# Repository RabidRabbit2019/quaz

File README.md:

# quaz
ветка проекта для платы на основе STM32G431CBU6

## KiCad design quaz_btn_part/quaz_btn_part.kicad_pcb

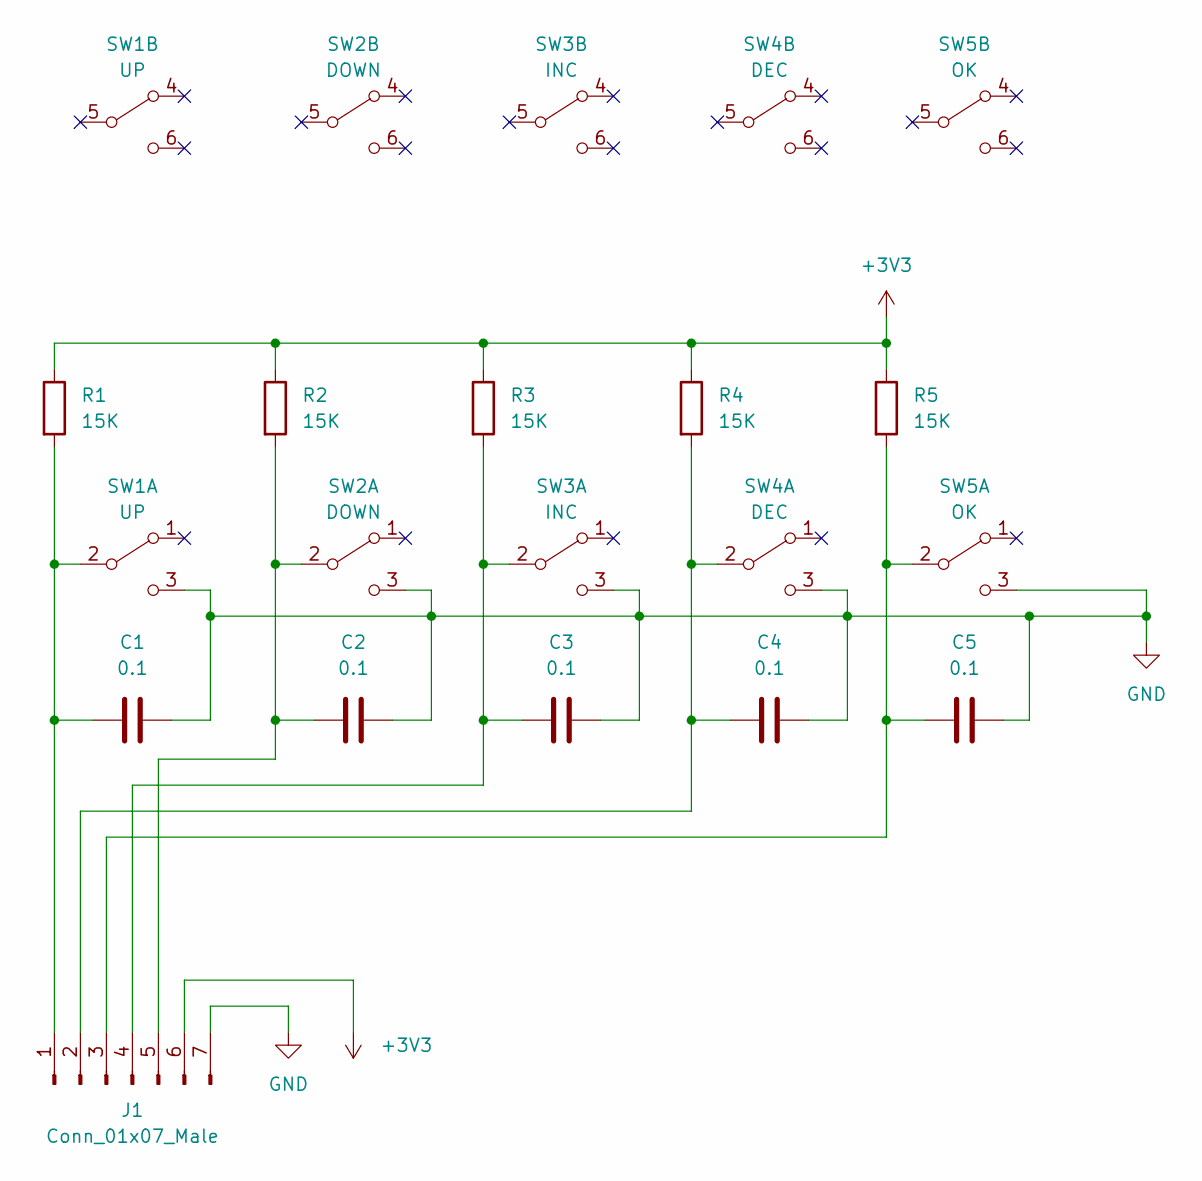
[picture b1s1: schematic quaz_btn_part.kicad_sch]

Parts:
C1, C2, C3, C4, C5: 0.1; C_1206_3216Metric_Pad1.33x1.80mm_HandSolder
J1: Conn_01x07_Male; PinHeader_1x07_P2.54mm_Vertical
R1, R2, R3, R4, R5: 15K; R_1206_3216Metric_Pad1.30x1.75mm_HandSolder
SW1: UP; BTN13
SW2: DOWN; BTN13
SW3: INC; BTN13
SW4: DEC; BTN13
SW5: OK; BTN13

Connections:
+3V3: J1.6, R1.1, R2.1, R3.1, R4.1, R5.1
GND: C1.2, C2.2, C3.2, C4.2, C5.2, J1.7, SW1.3 (C), SW2.3 (C), SW3.3 (C), SW4.3 (C), SW5.3 (C)
unnamed: C2.1, J1.5, R2.2, SW2.2 (B)
unnamed: C3.1, J1.4, R3.2, SW3.2 (B)
unnamed: C4.1, J1.2, R4.2, SW4.2 (B)
unnamed: C5.1, J1.3, R5.2, SW5.2 (B)
unnamed: C1.1, J1.1, R1.2, SW1.2 (B)

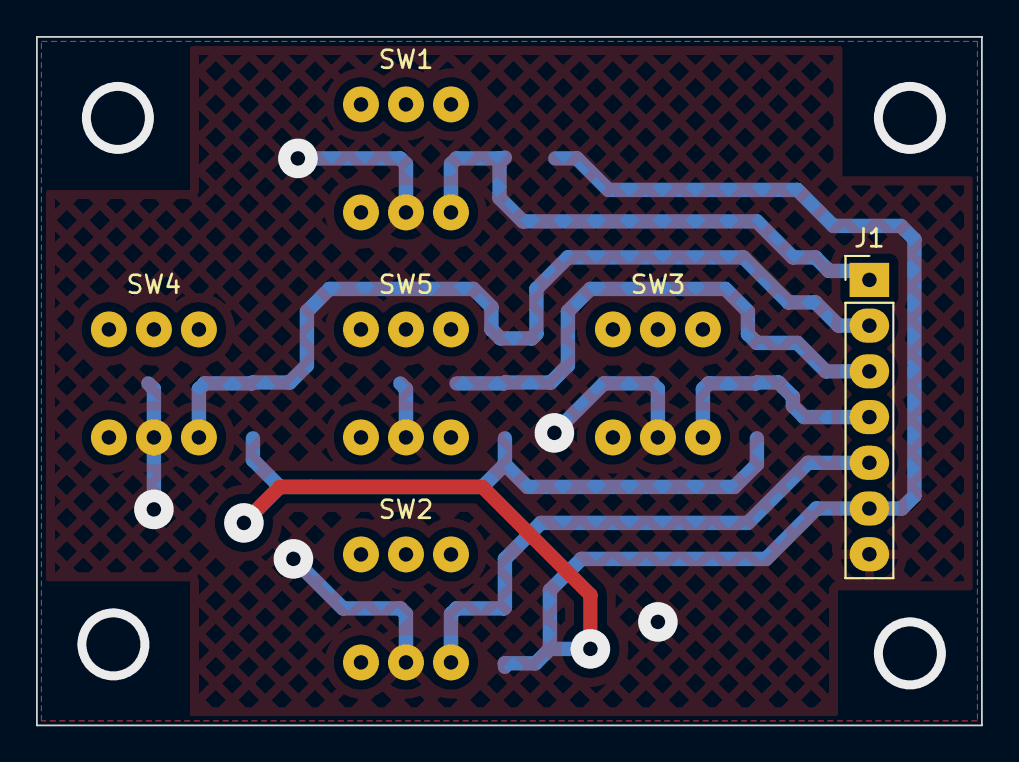
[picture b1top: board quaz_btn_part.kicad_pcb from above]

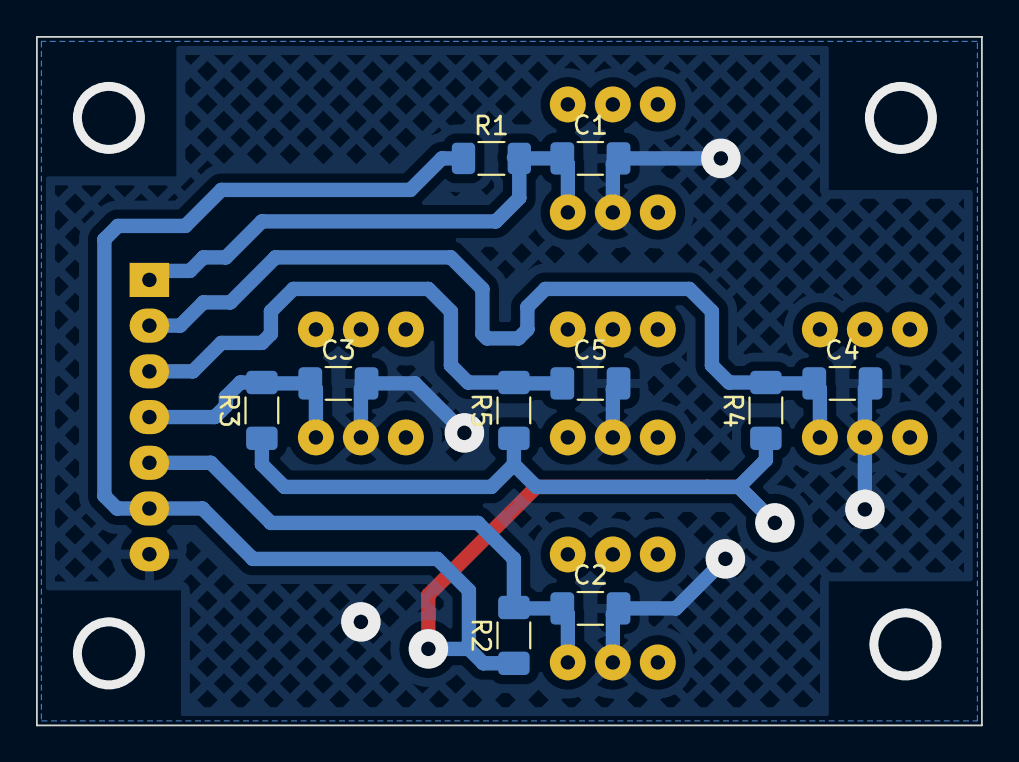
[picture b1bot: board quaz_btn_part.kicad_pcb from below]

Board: 2 copper layers, 52.5 x 38.2 mm, 16 parts (10 on the bottom side), 7 nets.

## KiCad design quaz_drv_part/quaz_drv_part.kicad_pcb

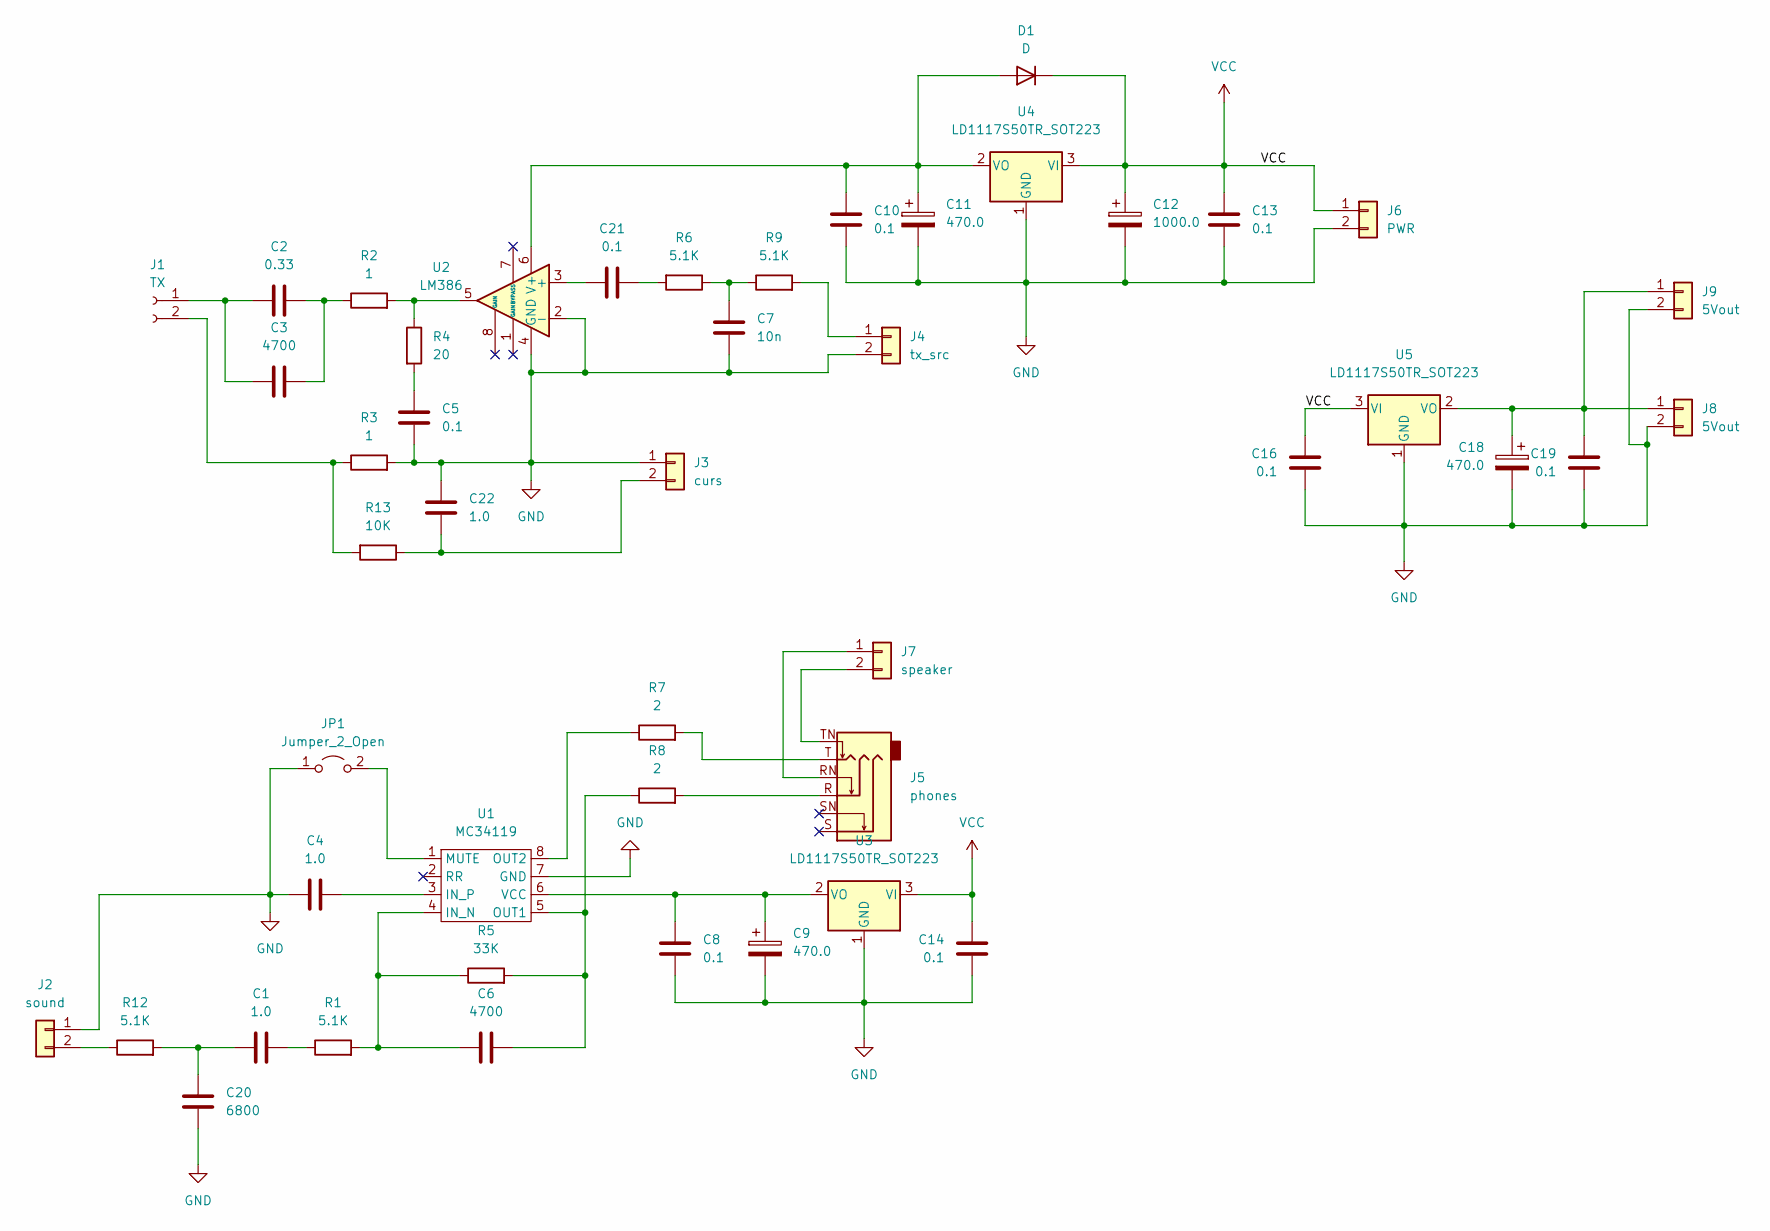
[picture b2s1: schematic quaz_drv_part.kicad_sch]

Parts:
C1, C4, C22: 1.0; C_1206_3216Metric_Pad1.33x1.80mm_HandSolder
C2: 0.33; C_Disc_D9.0mm_W5.0mm_P5.00mm
C3, C6: 4700; C_Disc_D9.0mm_W5.0mm_P5.00mm
C5, C8, C10, C13, C14, C16, C19, C21: 0.1; C_1206_3216Metric_Pad1.33x1.80mm_HandSolder
C7: 10n; C_Disc_D9.0mm_W5.0mm_P5.00mm
C9: 470.0; CP_Radial_D8.0mm_P5.00mm
C11, C18: 470.0; CP_Radial_D10.0mm_P5.00mm
C12: 1000.0; CP_Radial_D10.0mm_P5.00mm
C20: 6800; C_Disc_D9.0mm_W5.0mm_P5.00mm
D1: D; D_DO-41_SOD81_P5.08mm_Vertical_KathodeUp
J1: TX; PinHeader_1x02_P2.54mm_Vertical
J2: sound; PinHeader_1x02_P2.54mm_Vertical
J3: curs; PinHeader_1x02_P2.54mm_Vertical
J4: tx_src; PinHeader_1x02_P2.54mm_Vertical
J5: phones; Jack_6.35mm_Neutrik_NMJ6HCD3_Horizontal
J6: PWR; PinHeader_1x02_P2.54mm_Vertical
J7: speaker; PinHeader_1x02_P2.54mm_Vertical
J8, J9: 5Vout; PinHeader_1x02_P2.54mm_Vertical
JP1: Jumper_2_Open; PinHeader_1x02_P2.54mm_Vertical
R1, R6, R9, R12: 5.1K; R_1206_3216Metric_Pad1.30x1.75mm_HandSolder
R2, R3: 1; R_Axial_Power_L20.0mm_W6.4mm_P7.62mm_Vertical
R4: 20; R_Axial_DIN0207_L6.3mm_D2.5mm_P5.08mm_Vertical
R5: 33K; R_1206_3216Metric_Pad1.30x1.75mm_HandSolder
R7, R8: 2; R_1206_3216Metric_Pad1.30x1.75mm_HandSolder
R13: 10K; R_1206_3216Metric_Pad1.30x1.75mm_HandSolder
U1: MC34119; SOIC-8_3.9x4.9mm_P1.27mm
U2: LM386; DIP-8_W7.62mm
U3, U4, U5: LD1117S50TR_SOT223; SOT-223-3_TabPin2

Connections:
GND: C4.1, C5.2, C7.2, C8.2, C9.2, C10.2, C11.2, C12.2, C13.2, C14.2, C16.2, C18.2, C19.2, C20.2, C22.2, J2.1, J3.1, J4.2, J6.2, J8.2, J9.2, JP1.1 (A), R3.2, U1.7 (GND), U2.2 (-), U2.4 (GND), U3.1 (GND), U4.1 (GND), U5.1 (GND)
unnamed: C1.1, C20.1, R12.2
unnamed: C1.2, R1.1
unnamed: C2.1, C3.1, J1.1
unnamed: C2.2, C3.2, R2.1
unnamed: C4.2, U1.3 (IN_P)
unnamed: C5.1, R4.2
unnamed: C6.1, R5.2, R8.1, U1.5 (OUT1)
unnamed: C6.2, R1.2, R5.1, U1.4 (IN_N)
unnamed: C7.1, R6.1, R9.1
unnamed: C8.1, C9.1, U1.6 (VCC), U3.2 (VO)
unnamed: C10.1, C11.1, D1.2 (A), U2.6 (V+), U4.2 (VO)
unnamed: C18.1, C19.1, J8.1, J9.1, U5.2 (VO)
unnamed: C21.1, U2.3 (+)
unnamed: C21.2, R6.2
unnamed: C22.1, J3.2, R13.1
unnamed: J1.2, R3.1, R13.2
unnamed: J2.2, R12.1
unnamed: J4.1, R9.2
unnamed: J5.R, R8.2
unnamed: J5.RN, J7.1
unnamed: J5.T, R7.2
unnamed: J5.TN, J7.2
unnamed: JP1.2 (B), U1.1 (MUTE)
unnamed: R2.2, R4.1, U2.5
unnamed: R7.1, U1.8 (OUT2)
VCC: C12.1, C13.1, C14.1, C16.1, D1.1 (K), J6.1, U3.3 (VI), U4.3 (VI), U5.3 (VI)

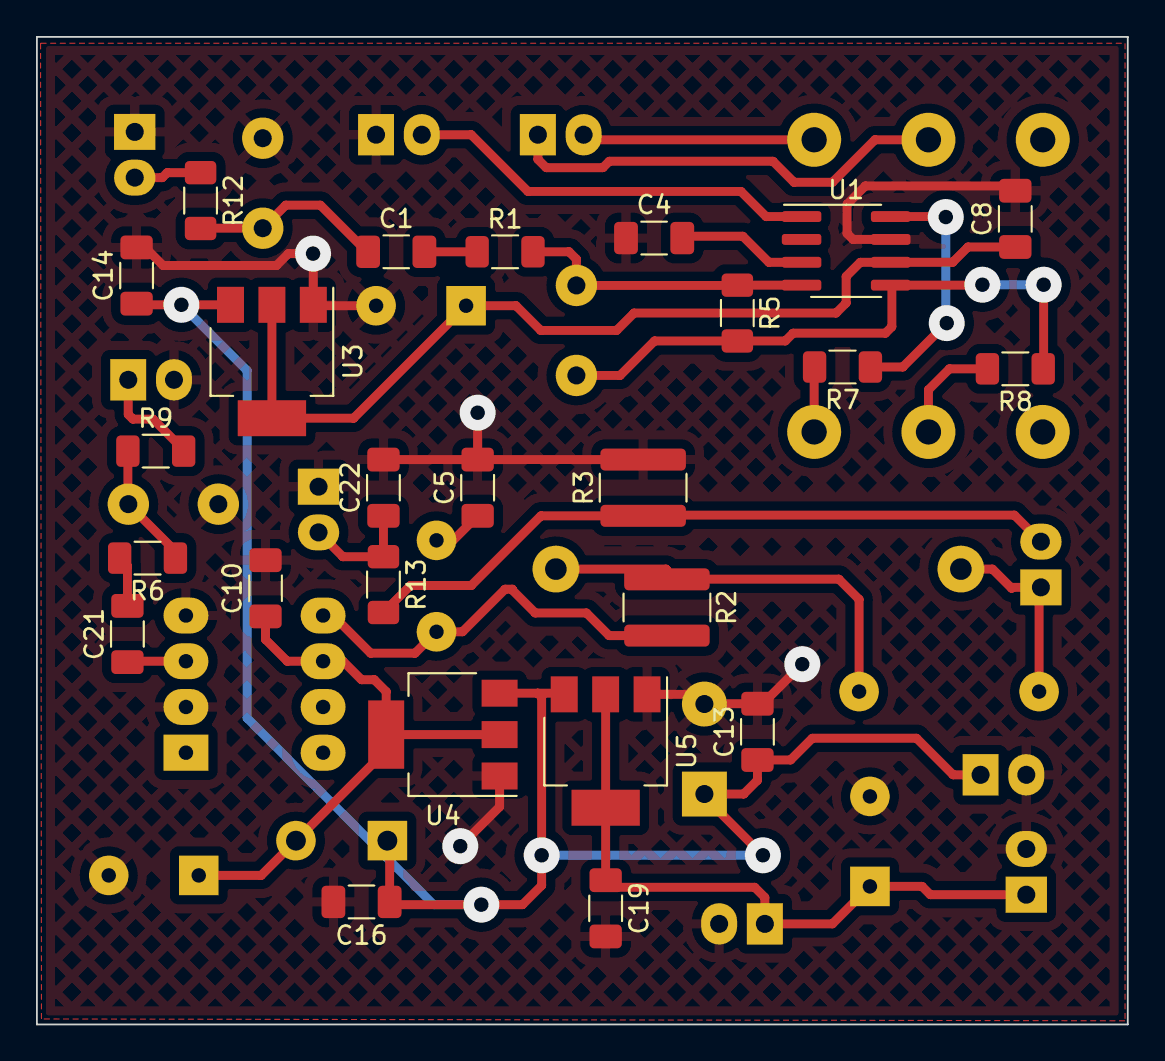
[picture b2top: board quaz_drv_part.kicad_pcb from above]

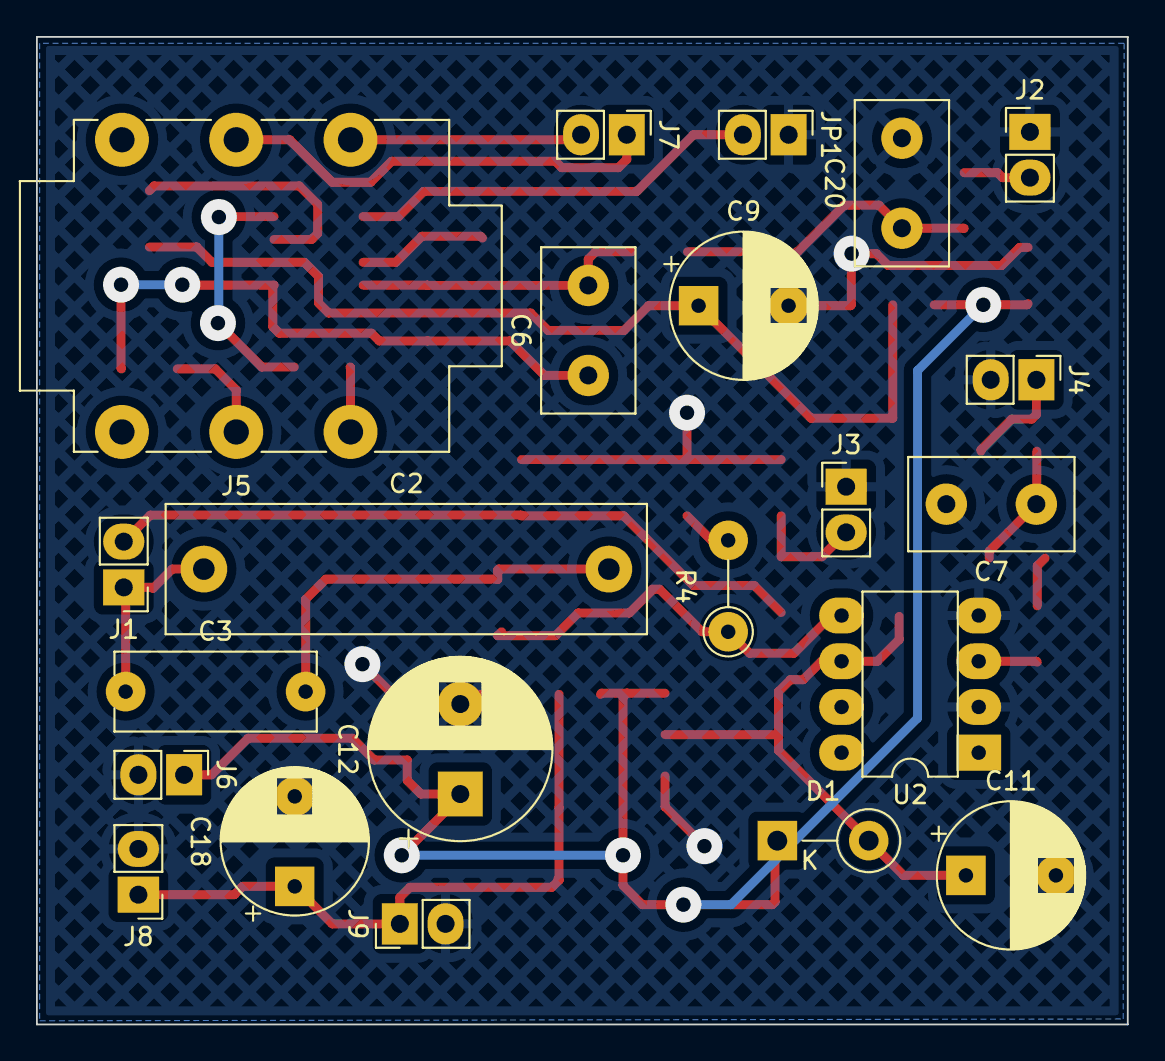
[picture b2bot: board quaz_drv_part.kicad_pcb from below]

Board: 2 copper layers, 60.6 x 54.9 mm, 47 parts (22 on the bottom side), 27 nets.

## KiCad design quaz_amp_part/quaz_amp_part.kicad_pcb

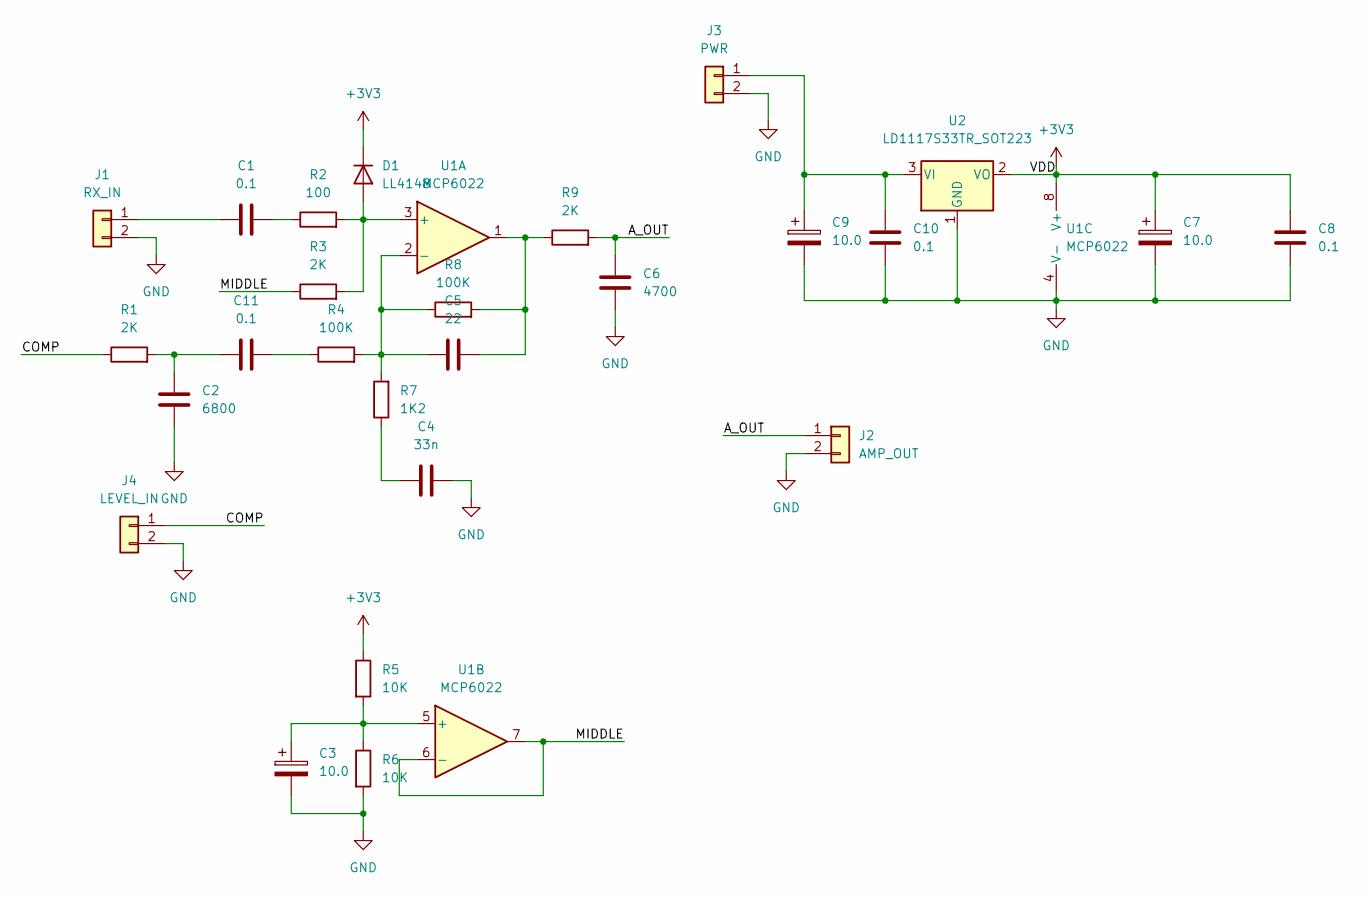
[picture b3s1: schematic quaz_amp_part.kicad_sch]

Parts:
C1, C8, C10, C11: 0.1; C_1206_3216Metric_Pad1.33x1.80mm_HandSolder
C2: 6800; C_Disc_D3.4mm_W2.1mm_P2.50mm
C3: 10.0; CP_EIA-7132-28_AVX-C_Pad2.72x3.50mm_HandSolder
C4: 33n; C_Disc_D8.0mm_W2.5mm_P5.00mm
C5: 22; C_Disc_D8.0mm_W2.5mm_P5.00mm
C6: 4700; C_Disc_D3.4mm_W2.1mm_P2.50mm
C7, C9: 10.0; CP_EIA-7132-20_AVX-U_Pad2.72x3.50mm_HandSolder
D1: LL4148; D_1206_3216Metric_Pad1.42x1.75mm_HandSolder
J1: RX_IN; PinHeader_1x02_P2.54mm_Vertical
J2: AMP_OUT; PinHeader_1x02_P2.54mm_Vertical
J3: PWR; PinHeader_1x02_P2.54mm_Vertical
J4: LEVEL_IN; PinHeader_1x02_P2.54mm_Vertical
R1, R3, R9: 2K; R_1206_3216Metric_Pad1.30x1.75mm_HandSolder
R2: 100; R_1206_3216Metric_Pad1.30x1.75mm_HandSolder
R4, R8: 100K; R_1206_3216Metric_Pad1.30x1.75mm_HandSolder
R5, R6: 10K; R_1206_3216Metric_Pad1.30x1.75mm_HandSolder
R7: 1K2; R_1206_3216Metric_Pad1.30x1.75mm_HandSolder
U1: MCP6022; SOIC-8_3.9x4.9mm_P1.27mm
U2: LD1117S33TR_SOT223; SOT-223-3_TabPin2

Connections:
+3V3: C7.1, C8.1, D1.1 (K), R5.1, U1.8 (V+), U2.2 (VO)
/A_OUT: C6.2, J2.1, R9.2
/COMP: J4.1, R1.1
/MIDDLE: R3.1, U1.6 (-), U1.7
GND: C2.2, C3.2, C4.2, C6.1, C7.2, C8.2, C9.2, C10.2, J1.2, J2.2, J3.2, J4.2, R6.2, U1.4 (V-), U2.1 (GND)
unnamed: C1.1, J1.1
unnamed: C1.2, R2.1
unnamed: C2.1, C11.1, R1.2
unnamed: C3.1, R5.2, R6.1, U1.5 (+)
unnamed: C4.1, R7.1
unnamed: C5.1, R4.2, R7.2, R8.1, U1.2 (-)
unnamed: C5.2, R8.2, R9.1, U1.1
unnamed: C9.1, C10.1, J3.1, U2.3 (VI)
unnamed: D1.2 (A), R2.2, R3.2, U1.3 (+)
unnamed: C11.2, R4.1

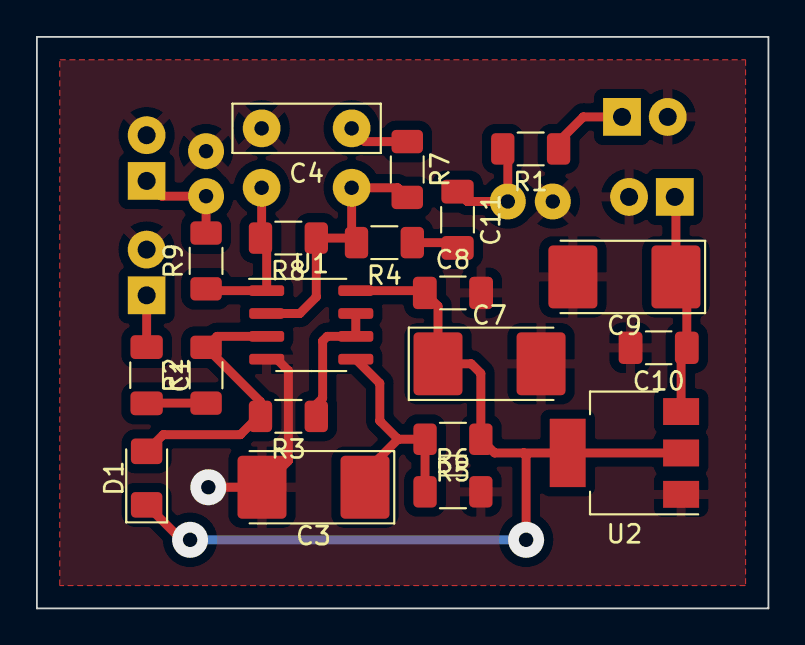
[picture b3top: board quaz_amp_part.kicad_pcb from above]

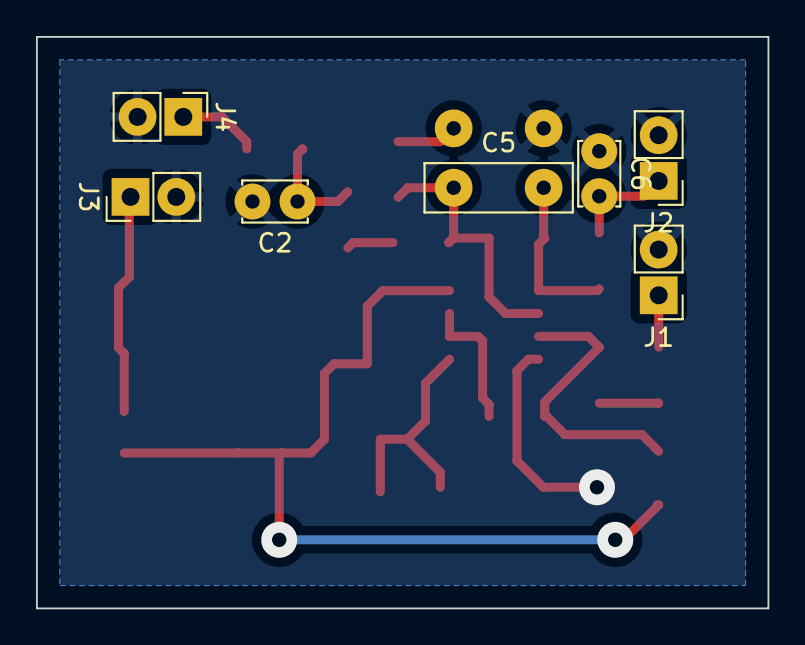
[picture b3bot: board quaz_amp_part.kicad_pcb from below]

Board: 2 copper layers, 40.6 x 31.8 mm, 27 parts (7 on the bottom side), 15 nets.

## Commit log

2024-03-18 initial, dds works
2024-03-19 adc double buffered
2024-03-20 next
2024-03-25 attach display test
2024-03-26 some minor changes
2024-03-27 change font
2024-03-29 add kicad sources
2024-03-29 more settings
2024-03-30 settings next
2024-04-01 buttons, gui
2024-04-13 use CORDIC arctan for vector length instead sqrt()
2024-04-15 drv layout change
2024-04-19 add btn_part
2024-04-25 add menu nav
2024-05-04 add current sens
2024-05-06 add rx settings
2024-05-06 fix buttons
2024-05-07 add buttons board
2024-05-15 add some settings
2024-05-16 remove some code
2024-06-14 pcb for buttons
2024-10-23 добавлены настройки вольтметра
2024-12-25 комментарии, новая версия файла stm32f103x6.h
2024-12-25 remove extra
2024-12-25 ветка для платы на STM32G431CBU6
2024-12-25 осталось немного
2024-12-25 экран работает
2024-12-25 PB8 не используется, кнопки PB10...PB14
2024-12-26 АЦП работает
2024-12-26 перключение каналов АЦП, сброс экрана
2024-12-29 добавлена обработка настроки ширины маски
2024-12-29 единая точка переключения каналов АЦП
2024-12-29 рефакторинг
2024-12-29 добавлена обработка интерфейса калибровки
2024-12-30 для контроля напряжения питания и тока в контуре используется ADC2
2025-03-07 ILI9341 -> ST7789
2025-03-14 добален флаг сборки
